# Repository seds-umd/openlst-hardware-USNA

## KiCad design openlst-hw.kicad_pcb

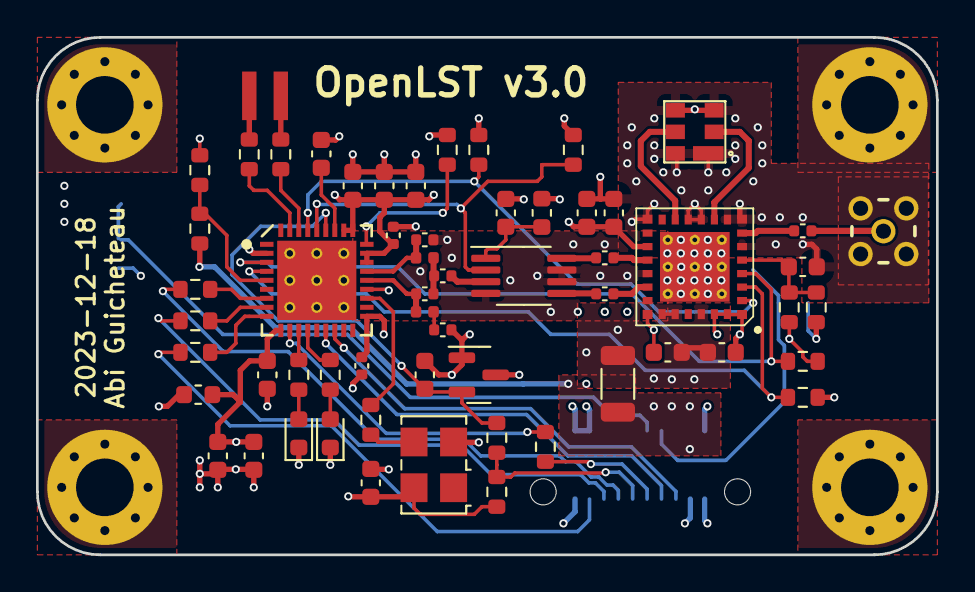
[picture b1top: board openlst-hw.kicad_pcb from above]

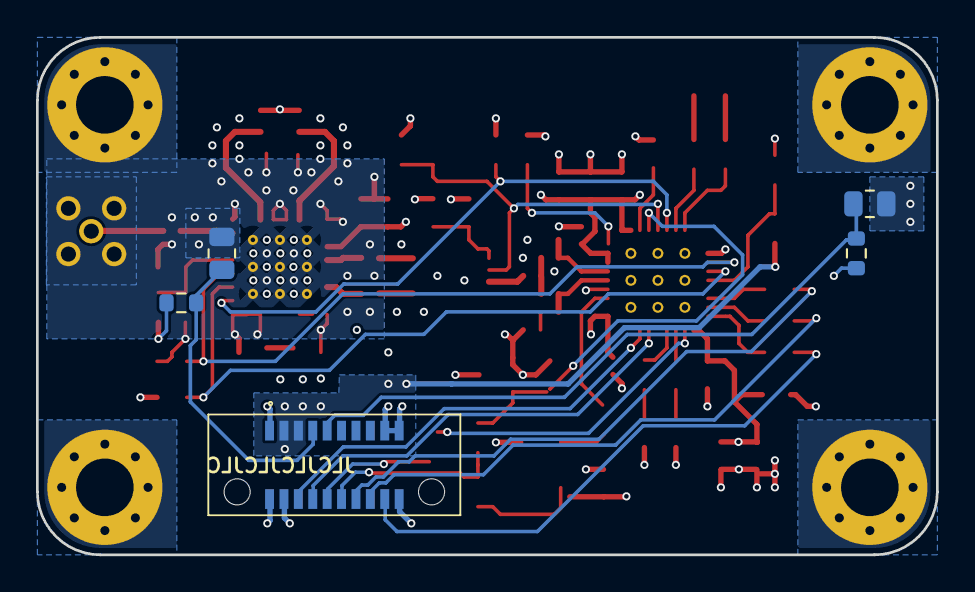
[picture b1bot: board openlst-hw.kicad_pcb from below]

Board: 4 copper layers, 50.0 x 28.8 mm, 69 parts (5 on the bottom side), 51 nets.

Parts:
C1, C3, C5, C8, C10, C11, C26: 0.1u; C_0603_1608Metric
C2, C7, C21, C25, C38, C39, C45: 220p; C_0402_1005Metric
C6: 0.22u; C_0603_1608Metric
C9, C44, C46, C47: 1u; C_0603_1608Metric
C19, C22: 1n; C_0603_1608Metric
C23, C24: 3.9p; C_0402_1005Metric
C27: 0.01u; C_0603_1608Metric
D1, D2: LED; LED_0603_1608Metric
H1, H2, H3, H4: M3 Hole; MountingHole_3.2mm_M3_Pad_Via
J3: Conn_02x10_Odd_Even; ERM8-010-YY.Y-XXX-DV-TR
J6: ANT; SAMTEC_MMCXV-J-P-HF-ST-TH1
L2: Z=1k @ 100M; L_1206_3216Metric
L3, L8: Z=1k @ 100M; L_0603_1608Metric
L5, L6: 27n; L_0402_1005Metric
R1, R2, R3, R4, R18, R26, R28: 1k; R_0603_1608Metric
R5, R6, R7, R8, R11, R12, R17: 100; R_0603_1608Metric
R9, R10, R22: 10k; R_0603_1608Metric
R16: 56k; R_0603_1608Metric
R21, R27: 33k; R_0603_1608Metric
R36: 6k8; R_0603_1608Metric
R37: 1k5; R_0603_1608Metric
TH1, TH2: Thermistor_NTC; R_0805_2012Metric
TP1, TP2: TestPoint; RCUCTE_0603_Test_Point
U2: CC1110; TI_CC_QFN36
U4: ASFL1-27.000MHZ; Oscillator_SMD_SeikoEpson_SG8002LB-4Pin_5.0x3.2mm
U5: MIC803; SOT-23
U6: PE4250; MSOP-8_3x3mm_P0.65mm
U7: RFFM6406; Qorvo_LGA_28_ThermalVias
U8: SF2446E; SAW-6_3.0mm

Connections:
+3V3: C27.1, J3.4, L3.1, L8.1, R1.2, R9.1, R10.1, R26.2, R27.2, R37.1, U4.4 (VCC), U5.3 (VDD)
/3V3_FILT: C1.1, C2.1, C3.1, C5.1, C7.1, C9.2, C10.1, C47.2, L3.2, U2.2 (DVDD), U2.10 (DVDD), U2.19 (AVDD), U2.22 (AVDD), U2.25 (AVDD), U2.26 (AVDD), U2.28 (GUARD), U2.29 (AVDD_DREG)
/AN0: R21.1, R22.2, U2.5 (P0_0)
/LST_TX_MODE: R1.1, U2.33 (P1_6), U7.2 (TR)
/PROG_DC: J3.6, U2.16 (P2_2)
/PROG_DD: J3.8, U2.15 (P2_1)
/RF_BYP: R28.1, U2.3 (P1_1), U7.4 (BYP)
/RF_EN: R26.1, U2.4 (P1_0), U7.3 (EN)
/UART0_RX: R11.2, TP1.1
/UART0_TX: R12.2, TP2.1
/UART_CTS_1: J3.14, R5.2
/UART_RTS_1: J3.16, R6.2
/UART_RX_1: J3.10, R8.2
/UART_TX_1: J3.18, R7.2
/VAA_FILT: C8.1, C11.1, C44.1, C46.1, L2.2, U7.17 (VCC_RX), U7.23 (VDD), U7.24 (VCC_TX1), U7.26 (VCC_TX2)
/~LST_RESET: J3.12, R18.2, R27.1
/~LST_RX_MODE: R2.1, U2.32 (P1_7), U6.2 (CTRL)
GND: C1.2, C2.2, C3.2, C5.2, C6.2, C7.2, C8.2, C9.1, C10.2, C11.2, C19.2, C21.1, C22.2, C23.1, C26.2, C27.2, C44.2, C46.2, C47.1, D1.1 (K), D2.1 (K), H1.1, H2.1, H3.1, H4.1, J3.1, J3.2, J3.17, J3.19, J3.20, J6.2 (Ext), R2.2, R16.1, R22.1, R28.2, R36.2, TH1.2, TH2.2, U2.37 (GND_PAD), U4.2 (GND), U5.1 (GND), U6.4 (GND), U6.6 (GND), U6.7 (GND), U7.1 (GND), U7.6 (GND), U7.8 (GND), U7.9 (GND), U7.11 (GND), U7.12 (GND), U7.15 (GND), U7.19 (GND), U7.21 (GND), U7.22 (GND), U7.27 (GND), U7.28 (GND), U7.29 (PAD), U8.1 (GND), U8.3 (GND), U8.4 (GND), U8.6 (GND)
unnamed: C21.2, L5.1
unnamed: C24.2, C25.1, L6.2
unnamed: D1.2 (A), R3.1
unnamed: D2.2 (A), R4.1
unnamed: C45.1, J6.1 (In)
unnamed: C19.1, U2.30 (DCOUPL)
unnamed: R5.1, U2.7 (P0_2)
unnamed: R6.1, U2.8 (P0_3)
unnamed: R7.1, U2.9 (P0_4)
unnamed: R8.1, U2.11 (P0_5)
unnamed: R3.2, U2.12 (P0_6)
unnamed: R4.2, U2.13 (P0_7)
unnamed: R11.1, U2.35 (P1_4)
unnamed: R12.1, U2.34 (P1_5)
unnamed: R16.2, U2.27 (RBIAS)
unnamed: C22.1, R18.1, U2.31 (RESET_N), U5.2 (~RESET)
unnamed: C23.2, L6.1, U2.24 (RF_N)
unnamed: C24.1, L5.2, U2.23 (RF_P)
unnamed: R17.2, U2.21 (XOSC-1)
unnamed: R17.1, U4.3 (OUT)
unnamed: C39.1, U6.5 (RF1)
unnamed: C38.1, U6.8 (RF2)
unnamed: C25.2, U6.3 (RFC)
unnamed: C26.1, L8.2, U6.1 (VDD)
unnamed: C45.2, U7.7 (ANT)
unnamed: C38.2, U7.18 (RX)
unnamed: U7.10 (SAW1), U8.2 (IN)
unnamed: U7.13 (SAW2), U8.5 (OUT)
unnamed: C39.2, U7.20 (TX)
unnamed: C6.1, R36.1, R37.2, U7.5 (VAPC)
TEMP_OUT_0: J3.7, R9.2, TH1.1
TEMP_OUT_1: J3.9, R10.2, TH2.1
VAA: J3.3, J3.5, L2.1, R21.2

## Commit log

2023-11-29 initial file transfer from openlst-hardware
2023-12-11 changed connectors, halfway through pcb
2023-12-18 finished edits v1
2023-12-19 finished edits v2
2023-12-20 Added hyperlynx sim
2023-12-30 fixed rf connection and power lines
2023-12-30 rotated ferrite bead and added 3d models
2023-12-30 wsl sucks
2023-12-30 changed 3d library
2024-01-05 added thermal reliefs and thermistors
2024-01-09 adjusted border and mounting holes
2024-01-27 changed thermistor part numbers
2024-01-27 changed bom to reflect obc
2024-01-30 adjusted BOM headers
2024-01-30 fixed typo in bom
2024-01-30 fixed TR components
2024-01-31 changed MMCXV-J-P-HF-ST-TH1 to a digikey part
2024-02-01 changed solder mask values in board setup
2024-02-03 added jlc order num
2024-02-13 Add interactive BOM
